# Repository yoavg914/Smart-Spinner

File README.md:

# Smart-Spinner
Project A - ECE Technion - Smart Spinner

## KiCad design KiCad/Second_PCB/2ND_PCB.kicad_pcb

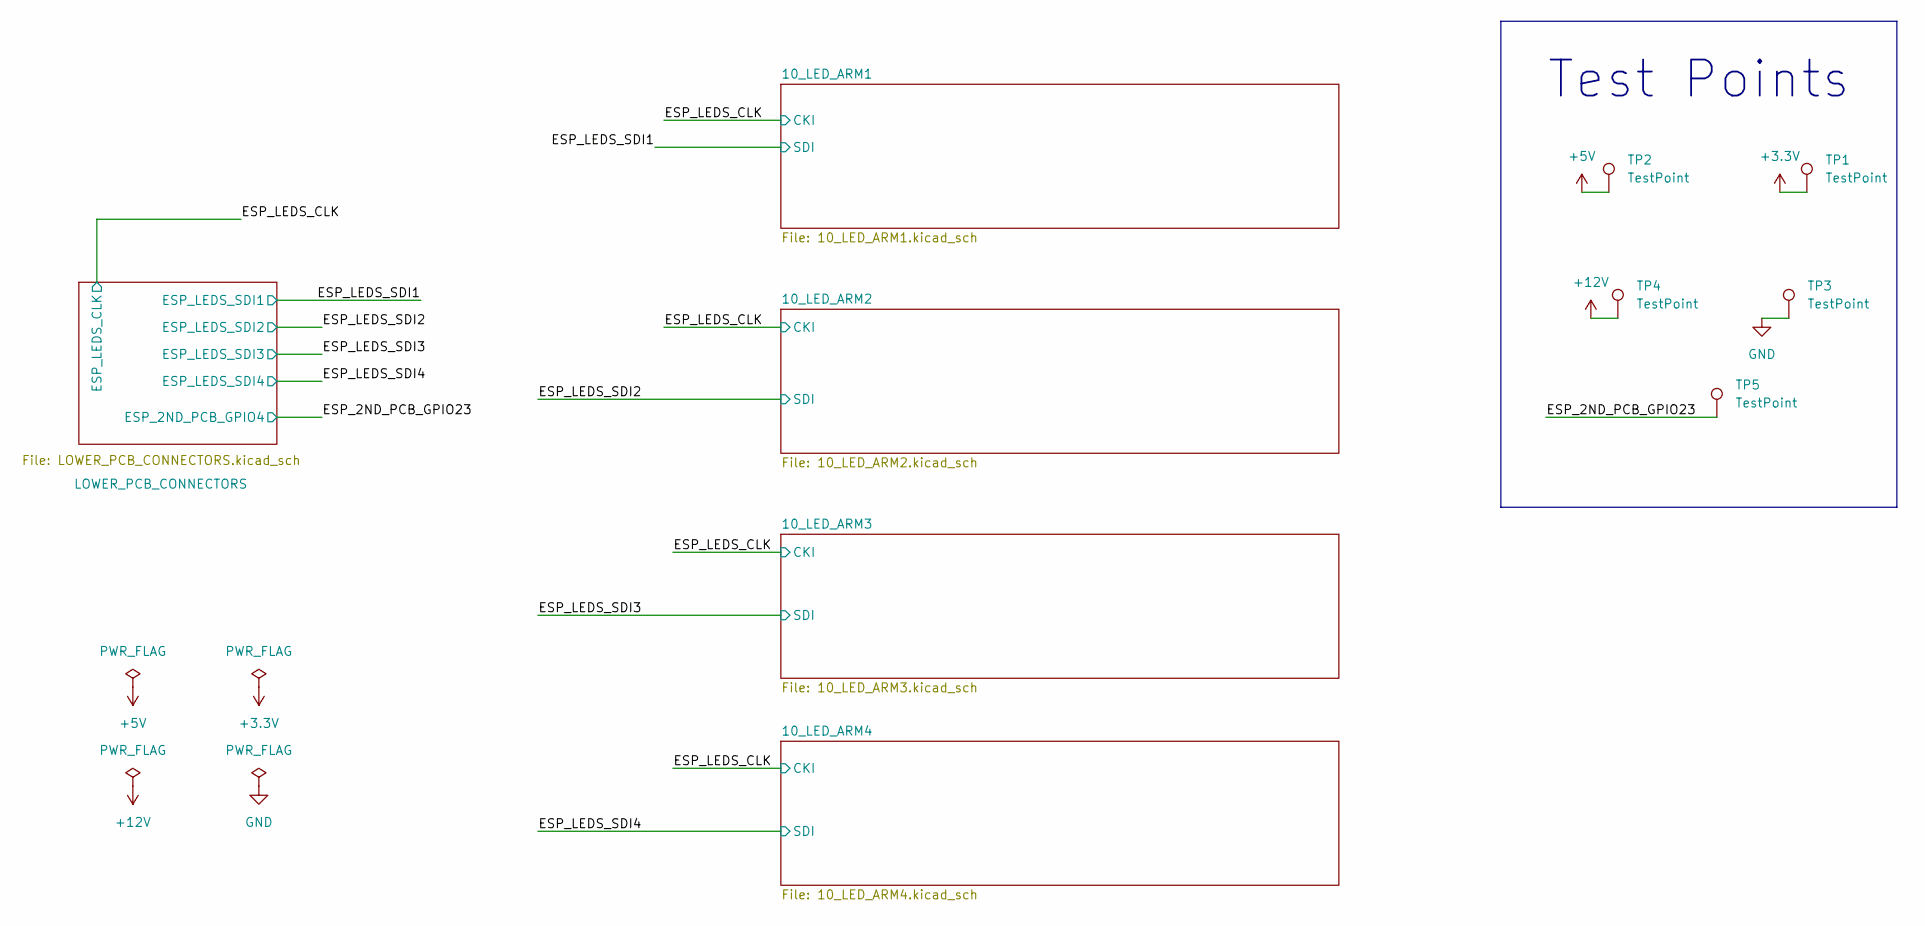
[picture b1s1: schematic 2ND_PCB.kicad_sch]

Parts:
TP1, TP2, TP3, TP4, TP5: TestPoint; TestPoint_Loop_D2.60mm_Drill1.4mm_Beaded

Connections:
+3.3V: TP1.1; also elsewhere on the board
+5V: TP2.1; also elsewhere on the board
+12V: TP4.1; also elsewhere on the board
/ESP_2ND_PCB_GPIO23: TP5.1; also elsewhere on the board
GND: TP3.1; also elsewhere on the board

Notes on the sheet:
Test Points

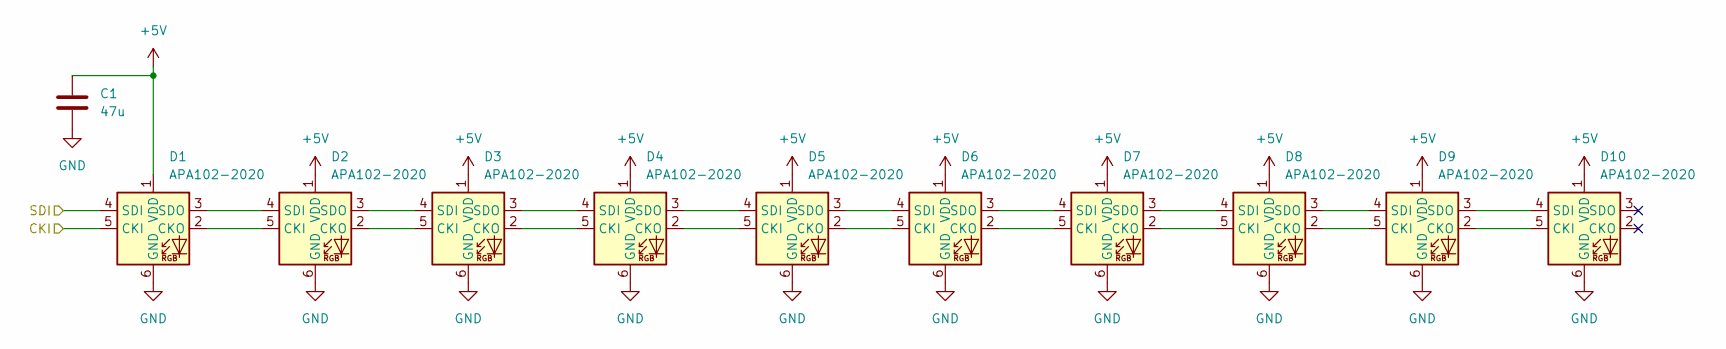
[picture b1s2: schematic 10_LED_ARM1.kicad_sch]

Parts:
C1: 47u; CP_EIA-3528-12_Kemet-T_HandSolder
D1, D2, D3, D4, D5, D6, D7, D8, D9, D10: APA102-2020; LED-APA102-2020_EDITED

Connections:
+5V: C1.1, D1.1 (VDD), D2.1 (VDD), D3.1 (VDD), D4.1 (VDD), D5.1 (VDD), D6.1 (VDD), D7.1 (VDD), D8.1 (VDD), D9.1 (VDD), D10.1 (VDD); also elsewhere on the board
/ESP_LEDS_CLK: D1.5 (CKI); also elsewhere on the board
/ESP_LEDS_SDI1: D1.4 (SDI); also elsewhere on the board
GND: C1.2, D1.6 (GND), D2.6 (GND), D3.6 (GND), D4.6 (GND), D5.6 (GND), D6.6 (GND), D7.6 (GND), D8.6 (GND), D9.6 (GND), D10.6 (GND); also elsewhere on the board
unnamed: D1.2 (CKO), D2.5 (CKI)
unnamed: D1.3 (SDO), D2.4 (SDI)
unnamed: D2.2 (CKO), D3.5 (CKI)
unnamed: D2.3 (SDO), D3.4 (SDI)
unnamed: D3.2 (CKO), D4.5 (CKI)
unnamed: D3.3 (SDO), D4.4 (SDI)
unnamed: D4.2 (CKO), D5.5 (CKI)
unnamed: D4.3 (SDO), D5.4 (SDI)
unnamed: D5.2 (CKO), D6.5 (CKI)
unnamed: D5.3 (SDO), D6.4 (SDI)
unnamed: D6.2 (CKO), D7.5 (CKI)
unnamed: D6.3 (SDO), D7.4 (SDI)
unnamed: D7.2 (CKO), D8.5 (CKI)
unnamed: D7.3 (SDO), D8.4 (SDI)
unnamed: D8.2 (CKO), D9.5 (CKI)
unnamed: D8.3 (SDO), D9.4 (SDI)
unnamed: D9.2 (CKO), D10.5 (CKI)
unnamed: D9.3 (SDO), D10.4 (SDI)

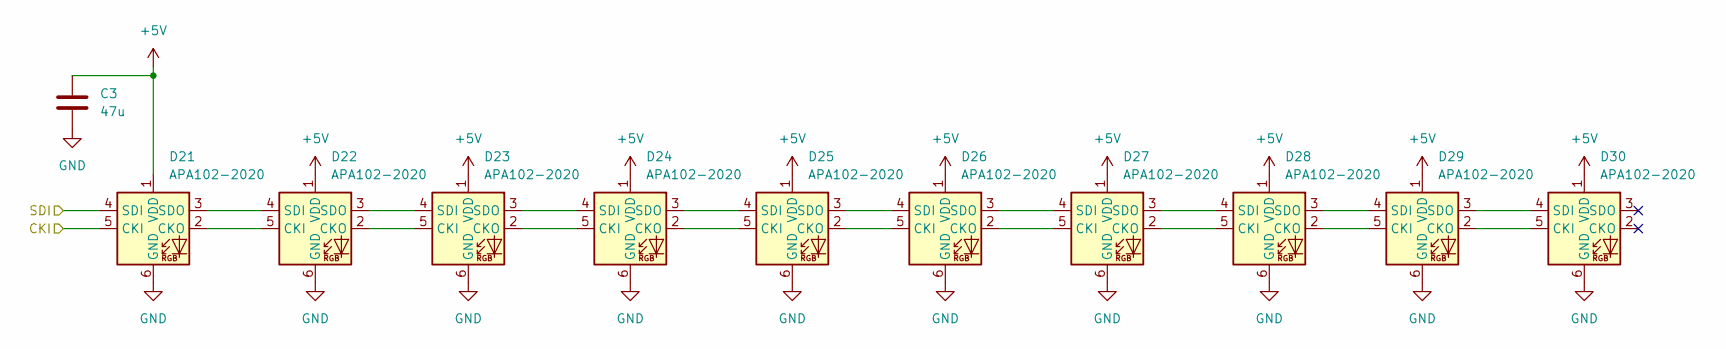
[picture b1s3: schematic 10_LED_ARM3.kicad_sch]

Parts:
C3: 47u; CP_EIA-3528-12_Kemet-T_HandSolder
D21, D22, D23, D24, D25, D26, D27, D28, D29, D30: APA102-2020; LED-APA102-2020_EDITED

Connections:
+5V: C3.1, D21.1 (VDD), D22.1 (VDD), D23.1 (VDD), D24.1 (VDD), D25.1 (VDD), D26.1 (VDD), D27.1 (VDD), D28.1 (VDD), D29.1 (VDD), D30.1 (VDD); also elsewhere on the board
/ESP_LEDS_CLK: D21.5 (CKI); also elsewhere on the board
/ESP_LEDS_SDI3: D21.4 (SDI); also elsewhere on the board
GND: C3.2, D21.6 (GND), D22.6 (GND), D23.6 (GND), D24.6 (GND), D25.6 (GND), D26.6 (GND), D27.6 (GND), D28.6 (GND), D29.6 (GND), D30.6 (GND); also elsewhere on the board
unnamed: D21.2 (CKO), D22.5 (CKI)
unnamed: D21.3 (SDO), D22.4 (SDI)
unnamed: D22.2 (CKO), D23.5 (CKI)
unnamed: D22.3 (SDO), D23.4 (SDI)
unnamed: D23.2 (CKO), D24.5 (CKI)
unnamed: D23.3 (SDO), D24.4 (SDI)
unnamed: D24.2 (CKO), D25.5 (CKI)
unnamed: D24.3 (SDO), D25.4 (SDI)
unnamed: D25.2 (CKO), D26.5 (CKI)
unnamed: D25.3 (SDO), D26.4 (SDI)
unnamed: D26.2 (CKO), D27.5 (CKI)
unnamed: D26.3 (SDO), D27.4 (SDI)
unnamed: D27.2 (CKO), D28.5 (CKI)
unnamed: D27.3 (SDO), D28.4 (SDI)
unnamed: D28.2 (CKO), D29.5 (CKI)
unnamed: D28.3 (SDO), D29.4 (SDI)
unnamed: D29.2 (CKO), D30.5 (CKI)
unnamed: D29.3 (SDO), D30.4 (SDI)

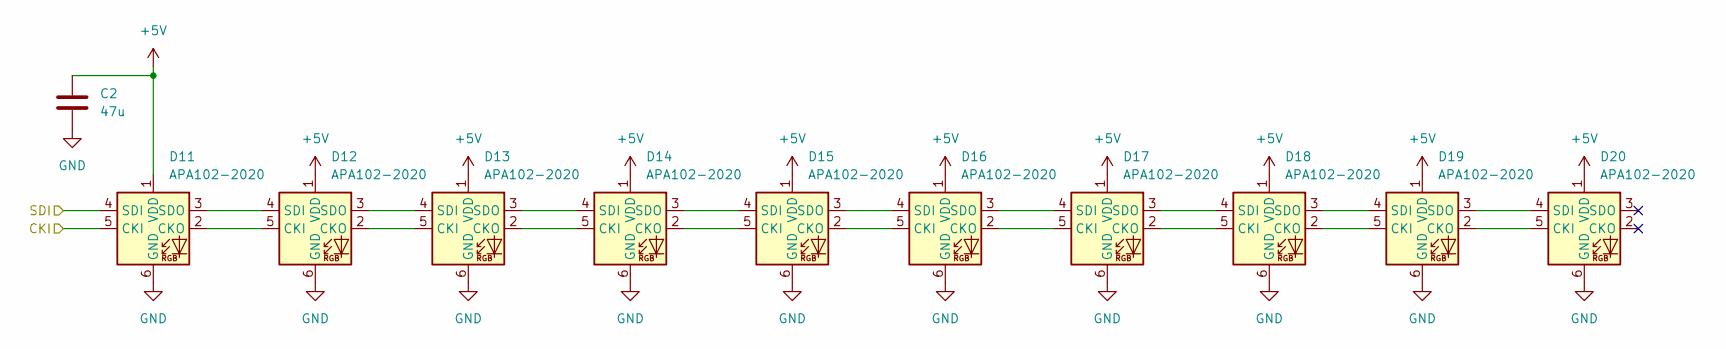
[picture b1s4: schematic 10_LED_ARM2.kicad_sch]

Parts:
C2: 47u; CP_EIA-3528-12_Kemet-T_HandSolder
D11, D12, D13, D14, D15, D16, D17, D18, D19, D20: APA102-2020; LED-APA102-2020_EDITED

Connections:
+5V: C2.1, D11.1 (VDD), D12.1 (VDD), D13.1 (VDD), D14.1 (VDD), D15.1 (VDD), D16.1 (VDD), D17.1 (VDD), D18.1 (VDD), D19.1 (VDD), D20.1 (VDD); also elsewhere on the board
/ESP_LEDS_CLK: D11.5 (CKI); also elsewhere on the board
/ESP_LEDS_SDI2: D11.4 (SDI); also elsewhere on the board
GND: C2.2, D11.6 (GND), D12.6 (GND), D13.6 (GND), D14.6 (GND), D15.6 (GND), D16.6 (GND), D17.6 (GND), D18.6 (GND), D19.6 (GND), D20.6 (GND); also elsewhere on the board
unnamed: D11.2 (CKO), D12.5 (CKI)
unnamed: D11.3 (SDO), D12.4 (SDI)
unnamed: D12.2 (CKO), D13.5 (CKI)
unnamed: D12.3 (SDO), D13.4 (SDI)
unnamed: D13.2 (CKO), D14.5 (CKI)
unnamed: D13.3 (SDO), D14.4 (SDI)
unnamed: D14.2 (CKO), D15.5 (CKI)
unnamed: D14.3 (SDO), D15.4 (SDI)
unnamed: D15.2 (CKO), D16.5 (CKI)
unnamed: D15.3 (SDO), D16.4 (SDI)
unnamed: D16.2 (CKO), D17.5 (CKI)
unnamed: D16.3 (SDO), D17.4 (SDI)
unnamed: D17.2 (CKO), D18.5 (CKI)
unnamed: D17.3 (SDO), D18.4 (SDI)
unnamed: D18.2 (CKO), D19.5 (CKI)
unnamed: D18.3 (SDO), D19.4 (SDI)
unnamed: D19.2 (CKO), D20.5 (CKI)
unnamed: D19.3 (SDO), D20.4 (SDI)

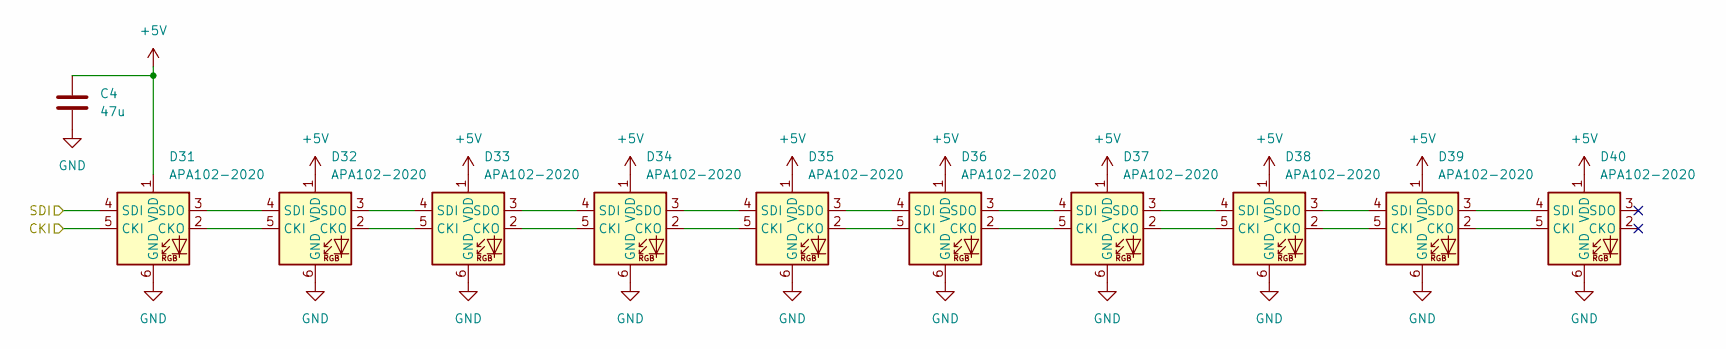
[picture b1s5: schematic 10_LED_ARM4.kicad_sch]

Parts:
C4: 47u; CP_EIA-3528-12_Kemet-T_HandSolder
D31, D32, D33, D34, D35, D36, D37, D38, D39, D40: APA102-2020; LED-APA102-2020_EDITED

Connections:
+5V: C4.1, D31.1 (VDD), D32.1 (VDD), D33.1 (VDD), D34.1 (VDD), D35.1 (VDD), D36.1 (VDD), D37.1 (VDD), D38.1 (VDD), D39.1 (VDD), D40.1 (VDD); also elsewhere on the board
/ESP_LEDS_CLK: D31.5 (CKI); also elsewhere on the board
/ESP_LEDS_SDI4: D31.4 (SDI); also elsewhere on the board
GND: C4.2, D31.6 (GND), D32.6 (GND), D33.6 (GND), D34.6 (GND), D35.6 (GND), D36.6 (GND), D37.6 (GND), D38.6 (GND), D39.6 (GND), D40.6 (GND); also elsewhere on the board
unnamed: D31.2 (CKO), D32.5 (CKI)
unnamed: D31.3 (SDO), D32.4 (SDI)
unnamed: D32.2 (CKO), D33.5 (CKI)
unnamed: D32.3 (SDO), D33.4 (SDI)
unnamed: D33.2 (CKO), D34.5 (CKI)
unnamed: D33.3 (SDO), D34.4 (SDI)
unnamed: D34.2 (CKO), D35.5 (CKI)
unnamed: D34.3 (SDO), D35.4 (SDI)
unnamed: D35.2 (CKO), D36.5 (CKI)
unnamed: D35.3 (SDO), D36.4 (SDI)
unnamed: D36.2 (CKO), D37.5 (CKI)
unnamed: D36.3 (SDO), D37.4 (SDI)
unnamed: D37.2 (CKO), D38.5 (CKI)
unnamed: D37.3 (SDO), D38.4 (SDI)
unnamed: D38.2 (CKO), D39.5 (CKI)
unnamed: D38.3 (SDO), D39.4 (SDI)
unnamed: D39.2 (CKO), D40.5 (CKI)
unnamed: D39.3 (SDO), D40.4 (SDI)

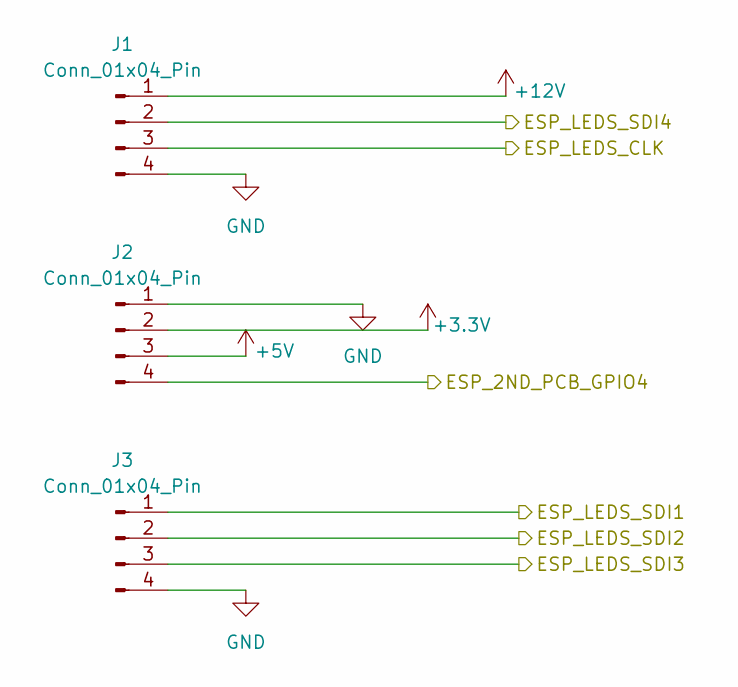
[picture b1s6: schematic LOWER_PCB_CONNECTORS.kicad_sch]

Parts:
J1, J2, J3: Conn_01x04_Pin; PinSocket_1x04_P2.54mm_Vertical

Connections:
+3.3V: J2.2; also elsewhere on the board
+5V: J2.3; also elsewhere on the board
+12V: J1.1; also elsewhere on the board
/ESP_2ND_PCB_GPIO23: J2.4; also elsewhere on the board
/ESP_LEDS_CLK: J1.3; also elsewhere on the board
/ESP_LEDS_SDI1: J3.1; also elsewhere on the board
/ESP_LEDS_SDI2: J3.2; also elsewhere on the board
/ESP_LEDS_SDI3: J3.3; also elsewhere on the board
/ESP_LEDS_SDI4: J1.2; also elsewhere on the board
GND: J1.4, J2.1, J3.4; also elsewhere on the board

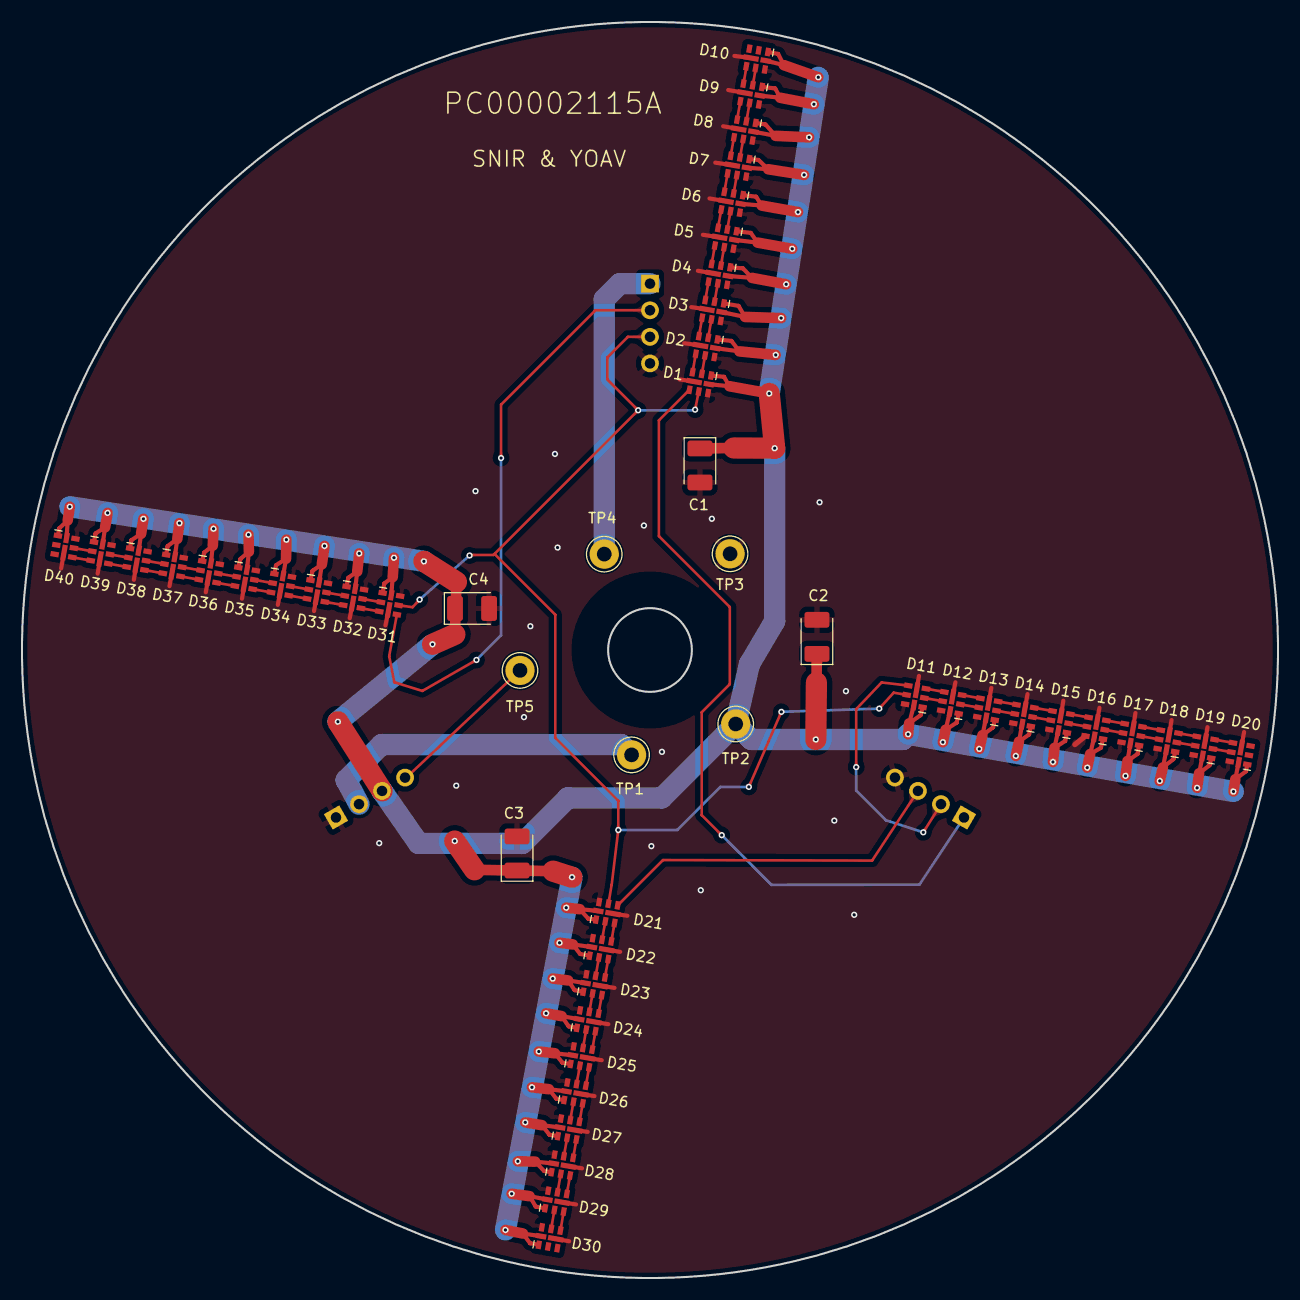
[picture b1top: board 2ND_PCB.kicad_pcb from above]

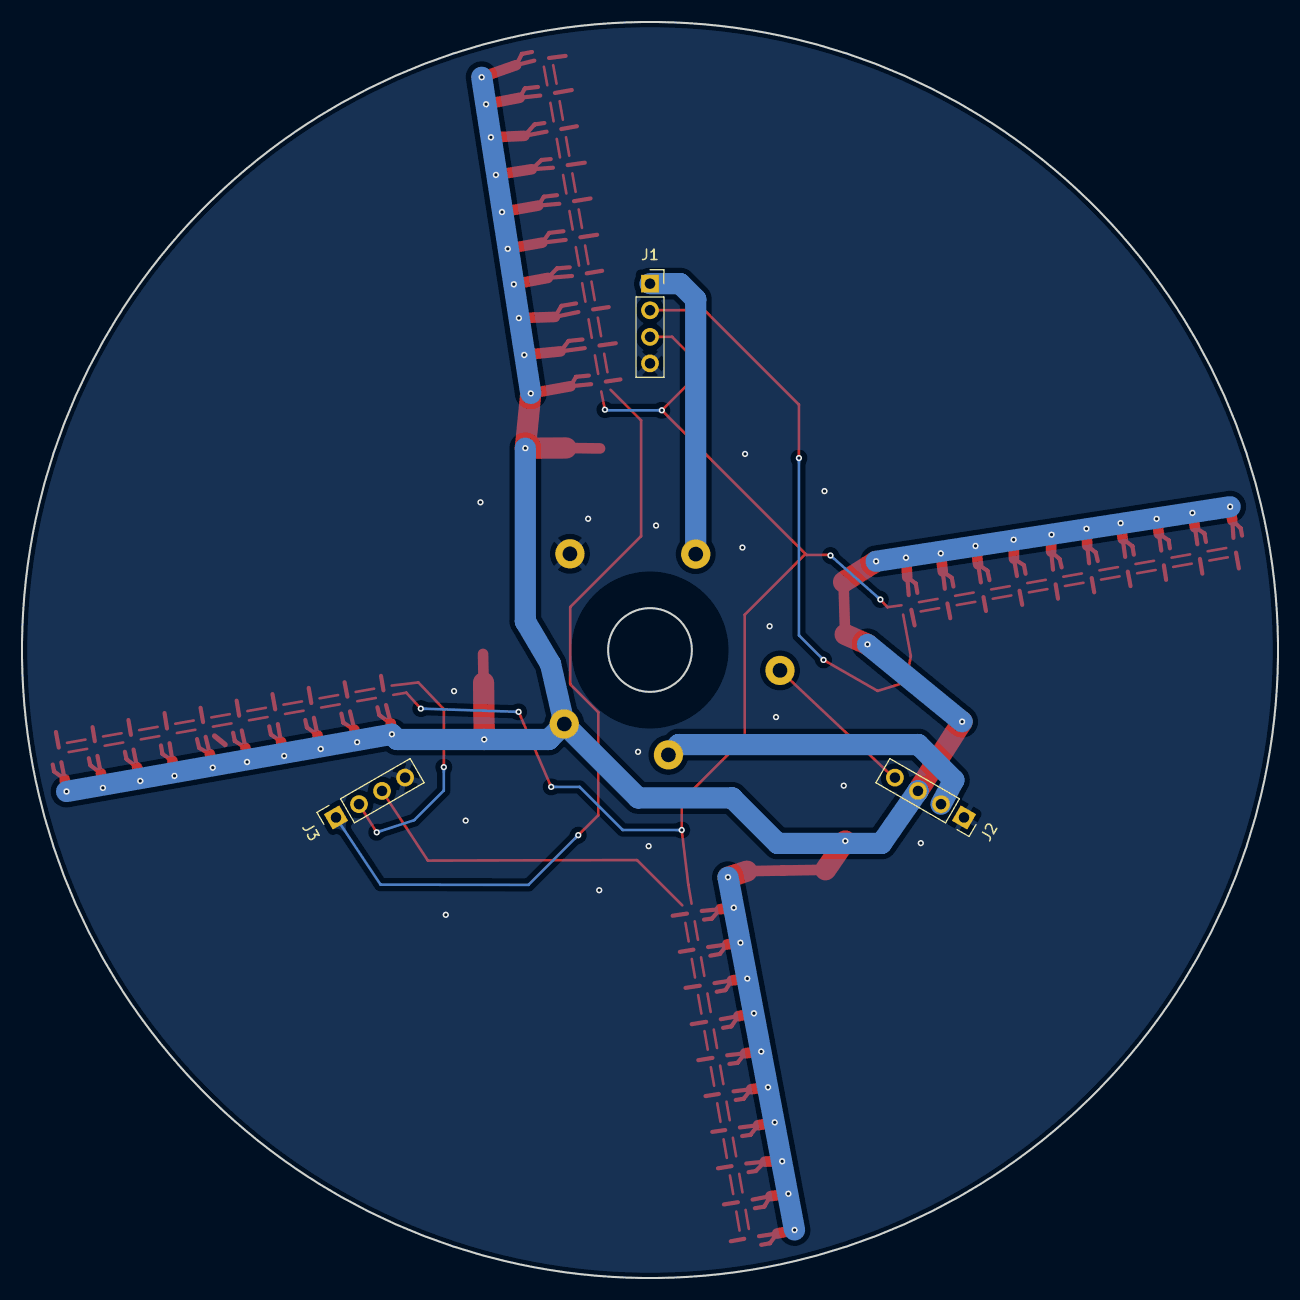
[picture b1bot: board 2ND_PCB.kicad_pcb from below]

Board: 2 copper layers, 120.0 x 120.0 mm, 52 parts (3 on the bottom side), 82 nets.

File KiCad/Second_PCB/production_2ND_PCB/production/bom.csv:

Designator,Footprint,Quantity,Value,LCSC Part #
"C1, C2, C3, C4",CP_EIA-3528-12_Kemet-T_HandSolder,4,47u,
"D1, D10, D11, D12, D13, D14, D15, D16, D17, D18, D19, D2, D20, D21, D22, D23, D24, D25, D26, D27, D28, D29, D3, D30, D31, D32, D33, D34, D35, D36, D37, D38, D39, D4, D40, D5, D6, D7, D8, D9",LED-APA102-2020_EDITED,40,APA102-2020,
"J1, J2, J3",PinSocket_1x04_P2.54mm_Vertical,3,Conn_01x04_Pin,
"TP1, TP2, TP3, TP4, TP5",TestPoint_Loop_D2.60mm_Drill1.4mm_Beaded,5,TestPoint,

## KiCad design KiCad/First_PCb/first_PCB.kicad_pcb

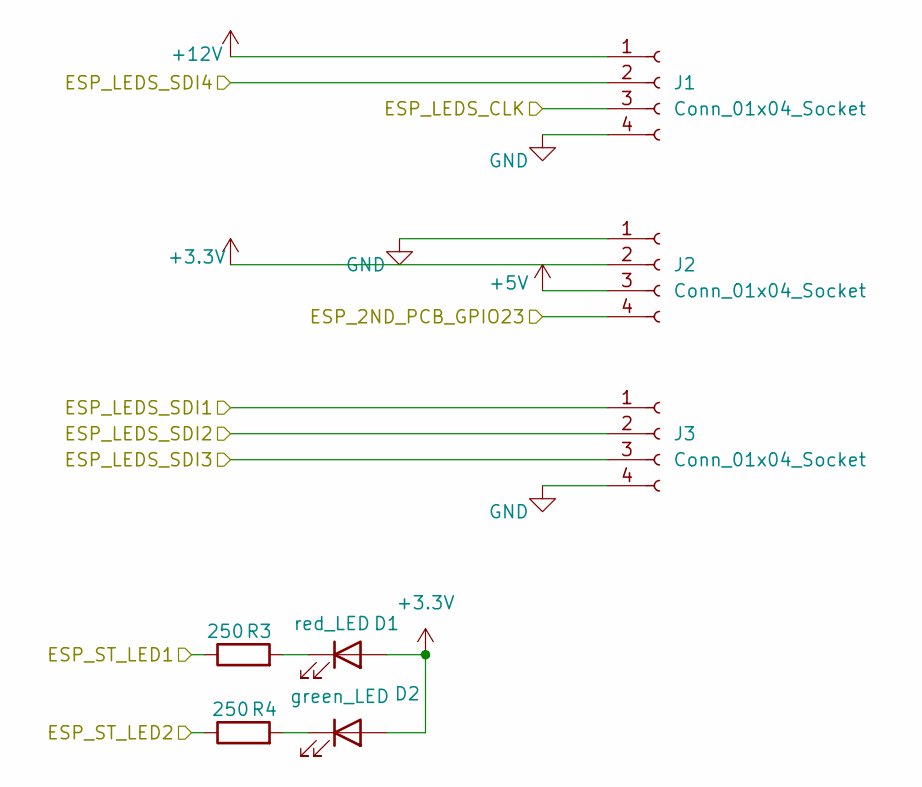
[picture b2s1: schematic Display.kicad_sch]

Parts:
D1: red_LED; LED_0603_1608Metric_Pad1.05x0.95mm_HandSolder
D2: green_LED; LED_0603_1608Metric_Pad1.05x0.95mm_HandSolder
J1, J2, J3: Conn_01x04_Socket; PinSocket_1x04_P2.54mm_Vertical
R3, R4: 250; R_0603_1608Metric_Pad0.98x0.95mm_HandSolder

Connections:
+3.3V: D1.2 (A), D2.2 (A), J2.2; also elsewhere on the board
+5V: J2.3; also elsewhere on the board
+12V: J1.1; also elsewhere on the board
/Processing/ESP_2ND_PCB_GPIO23: J2.4; also elsewhere on the board
/Processing/ESP_LEDS_CLK: J1.3; also elsewhere on the board
/Processing/ESP_LEDS_SDI1: J3.1; also elsewhere on the board
/Processing/ESP_LEDS_SDI2: J3.2; also elsewhere on the board
/Processing/ESP_LEDS_SDI3: J3.3; also elsewhere on the board
/Processing/ESP_LEDS_SDI4: J1.2; also elsewhere on the board
/Processing/ESP_ST_LED1: R3.1; also elsewhere on the board
/Processing/ESP_ST_LED2: R4.1; also elsewhere on the board
GND: J1.4, J2.1, J3.4; also elsewhere on the board
unnamed: D1.1 (K), R3.2
unnamed: D2.1 (K), R4.2

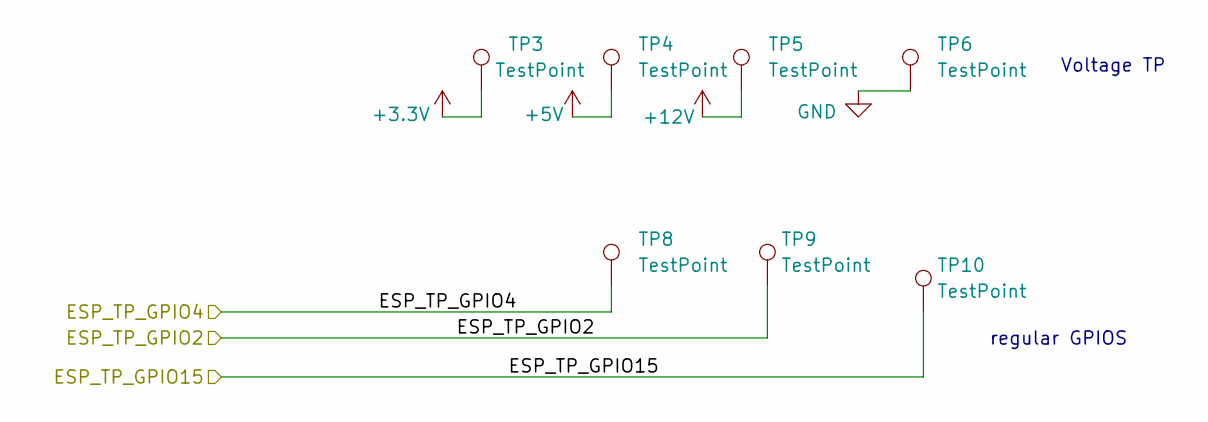
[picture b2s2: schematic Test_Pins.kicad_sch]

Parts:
TP3, TP4, TP5, TP6, TP8, TP9, TP10: TestPoint; TestPoint_Loop_D2.60mm_Drill1.4mm_Beaded

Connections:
+3.3V: TP3.1; also elsewhere on the board
+5V: TP4.1; also elsewhere on the board
+12V: TP5.1; also elsewhere on the board
/Processing/ESP_TP_GPIO2: TP9.1; also elsewhere on the board
/Processing/ESP_TP_GPIO15: TP10.1; also elsewhere on the board
/Test Pins/ESP_TP_GPIO4: TP8.1; also elsewhere on the board
GND: TP6.1; also elsewhere on the board

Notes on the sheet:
regular GPIOS
Voltage TP

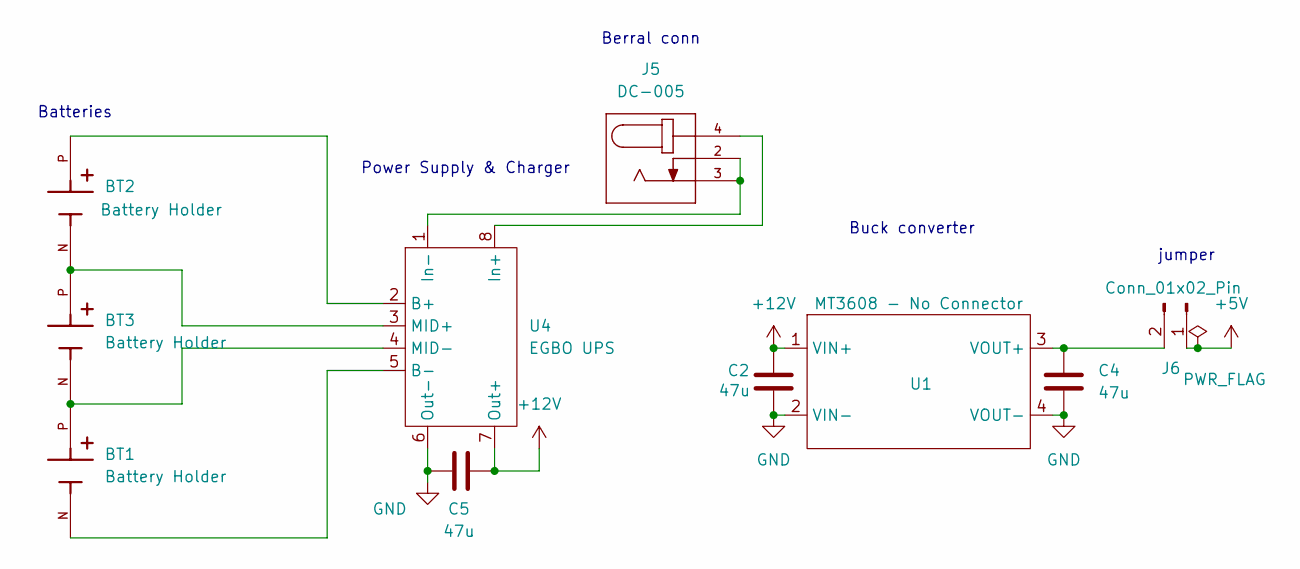
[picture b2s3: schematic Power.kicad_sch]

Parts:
BT1, BT2, BT3: Battery Holder; battery_holder
C2, C5: 47u; CP_EIA-6032-28_Kemet-C_HandSolder
C4: 47u; CP_EIA-3528-12_Kemet-T_HandSolder
J5: DC-005; NINIGI_DC-005
J6: Conn_01x02_Pin; PinHeader_1x02_P2.54mm_Vertical
U1: MT3608 - No Connector; MT3608_no_conn_TH
U4: EGBO UPS; PWR_SPLY12V_TH

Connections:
+5V: J6.1; also elsewhere on the board
+12V: C2.1, C5.2, U1.1 (VIN+), U4.7 (Out+); also elsewhere on the board
GND: C2.2, C4.2, C5.1, U1.2 (VIN-), U1.4 (VOUT-), U4.6 (Out-); also elsewhere on the board
unnamed: C4.1, J6.2, U1.3 (VOUT+)
unnamed: BT2.P, U4.2 (B+)
unnamed: BT1.N, U4.5 (B-)
unnamed: J5.4, U4.8 (In+)
unnamed: J5.2, J5.3, U4.1 (In-)
unnamed: BT2.N, BT3.P, U4.3 (MID+)
unnamed: BT1.P, BT3.N, U4.4 (MID-)

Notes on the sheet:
Berral conn
Batteries
jumper
Power Supply & Charger
Buck converter

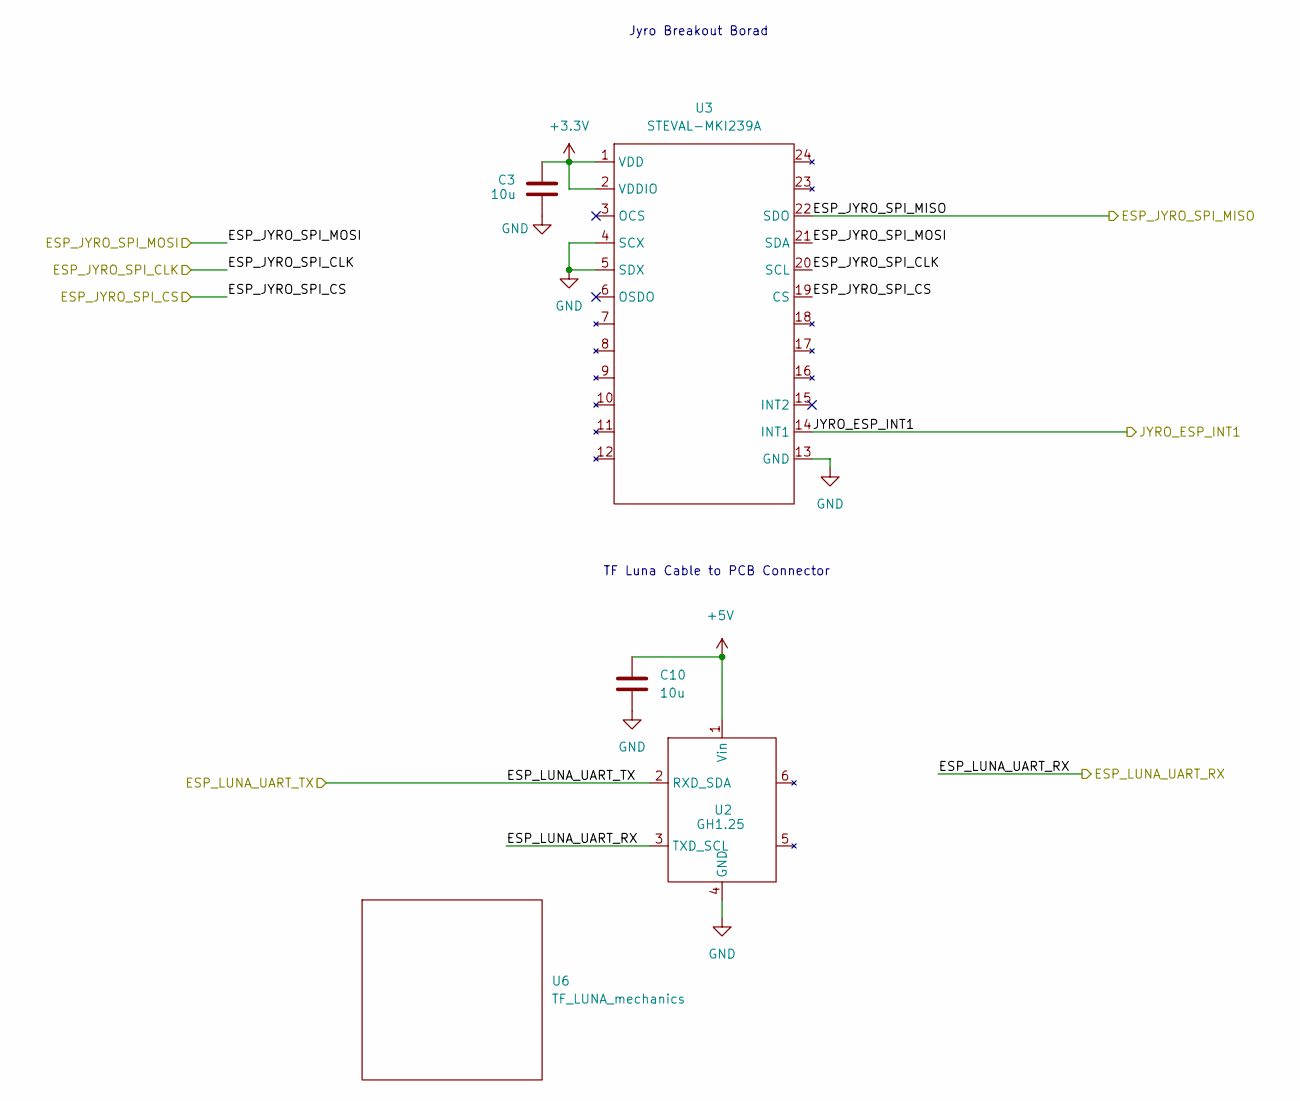
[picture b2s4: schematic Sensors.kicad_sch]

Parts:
C3, C10: 10u; C_0603_1608Metric_Pad1.08x0.95mm_HandSolder
U2: GH1.25; JST_GH125
U3: STEVAL-MKI239A
U6: TF_LUNA_mechanics

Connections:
+3.3V: C3.1, U3.1 (VDD), U3.2 (VDDIO); also elsewhere on the board
+5V: C10.1, U2.1 (Vin); also elsewhere on the board
/Processing/ESP_JYRO_SPI_CLK: U3.20 (SCL); also elsewhere on the board
/Processing/ESP_JYRO_SPI_CS: U3.19 (CS); also elsewhere on the board
/Processing/ESP_JYRO_SPI_MISO: U3.22 (SDO); also elsewhere on the board
/Processing/ESP_JYRO_SPI_MOSI: U3.21 (SDA); also elsewhere on the board
/Processing/ESP_LUNA_UART_RX: U2.3 (TXD_SCL); also elsewhere on the board
/Processing/ESP_LUNA_UART_TX: U2.2 (RXD_SDA); also elsewhere on the board
/Processing/JYRO_ESP_INT1: U3.14 (INT1); also elsewhere on the board
GND: C3.2, C10.2, U2.4 (GND), U3.4 (SCX), U3.5 (SDX), U3.13 (GND); also elsewhere on the board

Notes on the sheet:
TF Luna Cable to PCB Connector
Jyro Breakout Borad

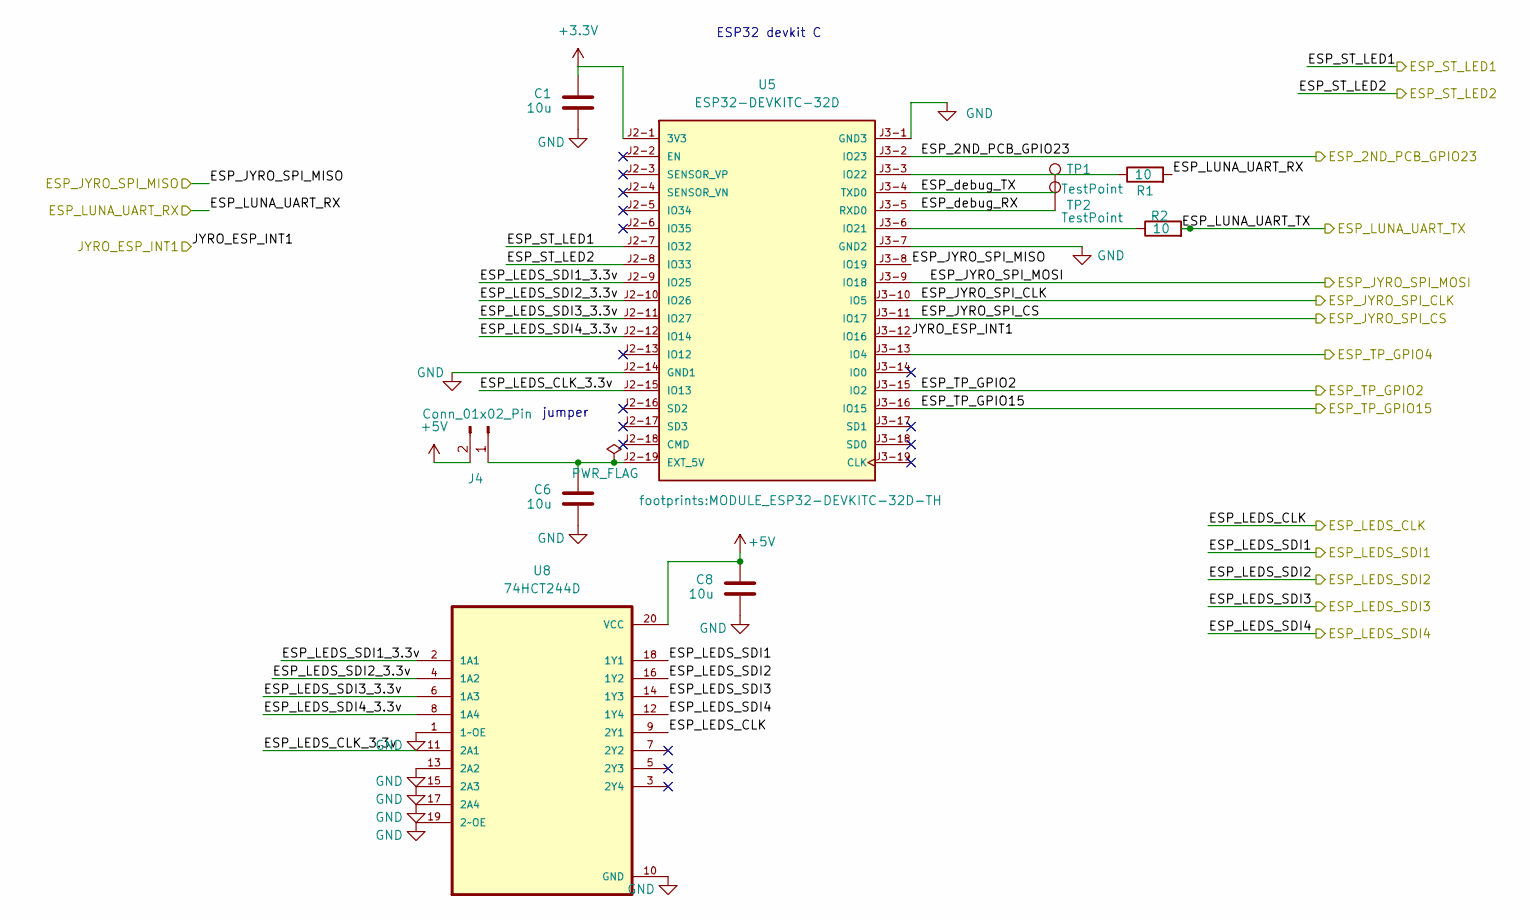
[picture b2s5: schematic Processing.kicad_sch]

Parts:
C1, C6, C8: 10u; C_0603_1608Metric_Pad1.08x0.95mm_HandSolder
J4: Conn_01x02_Pin; PinHeader_1x02_P2.54mm_Vertical
R1, R2: 10; R_0603_1608Metric_Pad0.98x0.95mm_HandSolder
TP1, TP2: TestPoint; TestPoint_Loop_D2.60mm_Drill1.4mm_Beaded
U5: ESP32-DEVKITC-32D; MODULE_ESP32-DEVKITC-32D-TH; PARTREV V4
U8: 74HCT244D; 74HCT244D-SOIC20; DigiKey_Part_Number 2156-SN74HCT244DW-ND

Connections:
+3.3V: C1.1, U5.J2-1 (3V3); also elsewhere on the board
+5V: C8.1, J4.2, U8.20 (VCC); also elsewhere on the board
/Processing/ESP_2ND_PCB_GPIO23: U5.J3-2 (IO23); also elsewhere on the board
/Processing/ESP_JYRO_SPI_CLK: U5.J3-10 (IO5); also elsewhere on the board
/Processing/ESP_JYRO_SPI_CS: U5.J3-11 (IO17); also elsewhere on the board
/Processing/ESP_JYRO_SPI_MISO: U5.J3-8 (IO19); also elsewhere on the board
/Processing/ESP_JYRO_SPI_MOSI: U5.J3-9 (IO18); also elsewhere on the board
/Processing/ESP_LEDS_CLK: U8.9 (2Y1); also elsewhere on the board
/Processing/ESP_LEDS_CLK_3.3v: U5.J2-15 (IO13), U8.11 (2A1)
/Processing/ESP_LEDS_SDI1: U8.18 (1Y1); also elsewhere on the board
/Processing/ESP_LEDS_SDI1_3.3v: U5.J2-9 (IO25), U8.2 (1A1)
/Processing/ESP_LEDS_SDI2: U8.16 (1Y2); also elsewhere on the board
/Processing/ESP_LEDS_SDI2_3.3v: U5.J2-10 (IO26), U8.4 (1A2)
/Processing/ESP_LEDS_SDI3: U8.14 (1Y3); also elsewhere on the board
/Processing/ESP_LEDS_SDI3_3.3v: U5.J2-11 (IO27), U8.6 (1A3)
/Processing/ESP_LEDS_SDI4: U8.12 (1Y4); also elsewhere on the board
/Processing/ESP_LEDS_SDI4_3.3v: U5.J2-12 (IO14), U8.8 (1A4)
/Processing/ESP_LUNA_UART_RX: R1.2; also elsewhere on the board
/Processing/ESP_LUNA_UART_TX: R2.2; also elsewhere on the board
/Processing/ESP_ST_LED1: U5.J2-7 (IO32); also elsewhere on the board
/Processing/ESP_ST_LED2: U5.J2-8 (IO33); also elsewhere on the board
/Processing/ESP_TP_GPIO2: U5.J3-15 (IO2); also elsewhere on the board
/Processing/ESP_TP_GPIO15: U5.J3-16 (IO15); also elsewhere on the board
/Processing/ESP_debug_RX: TP2.1, U5.J3-5 (RXD0)
/Processing/ESP_debug_TX: TP1.1, U5.J3-4 (TXD0)
/Processing/JYRO_ESP_INT1: U5.J3-12 (IO16); also elsewhere on the board
/Test Pins/ESP_TP_GPIO4: U5.J3-13 (IO4); also elsewhere on the board
GND: C1.2, C6.2, C8.2, U5.J2-14 (GND1), U5.J3-1 (GND3), U5.J3-7 (GND2), U8.1 (1~OE), U8.10 (GND), U8.13 (2A2), U8.15 (2A3), U8.17 (2A4), U8.19 (2~OE); also elsewhere on the board
unnamed: C6.1, J4.1, U5.J2-19 (EXT_5V)
unnamed: R2.1, U5.J3-6 (IO21)
unnamed: R1.1, U5.J3-3 (IO22)

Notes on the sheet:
jumper
ESP32 devkit C
